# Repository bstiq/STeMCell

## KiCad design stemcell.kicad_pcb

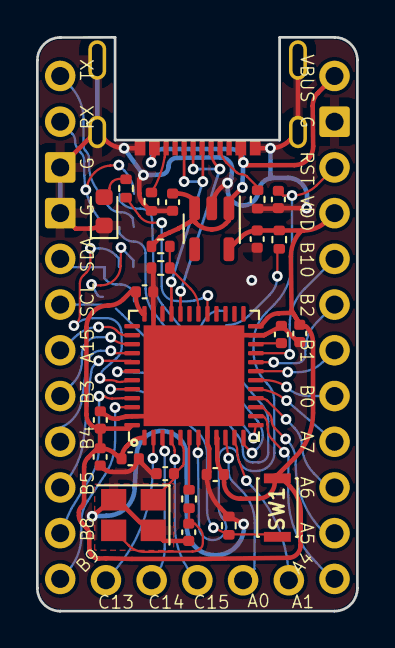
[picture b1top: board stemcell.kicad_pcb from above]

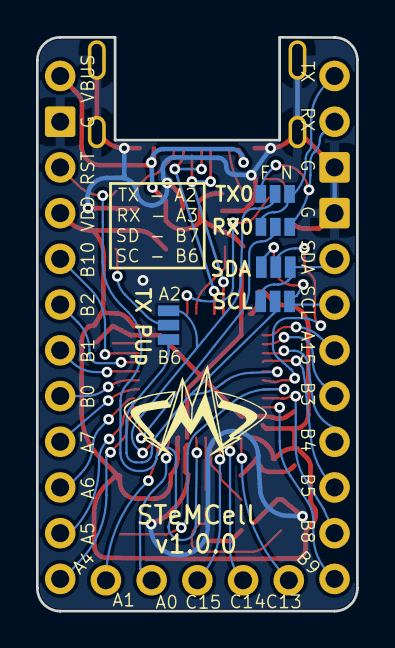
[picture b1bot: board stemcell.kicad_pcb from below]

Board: 2 copper layers, 17.8 x 31.9 mm, 34 parts (5 on the bottom side), 44 nets.

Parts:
C1: 10u; C_0402_1005Metric
C2, C3, C9: 4.7u; C_0402_1005Metric
C4, C5, C6, C7, C8, C12: 100n; C_0402_1005Metric
C10, C11: 20p; C_0402_1005Metric
D1: LED; LED_0603_1608Metric
J1: USB C Connector; USB-C-C168688
J2: Left; Pins12
J3: Right; Pins12
J4: Down; Pins5
JP1: TX0; SOLDER_JUMPER_3
JP2: RX0; SOLDER_JUMPER_3
JP3: SDA; SOLDER_JUMPER_3
JP4: SCL; SOLDER_JUMPER_3
JP5: TX PUp; SOLDER_JUMPER_3
R1: 220; R_0402_1005Metric
R2, R3: 5k1; R_0402_1005Metric
R4: 2k2; R_0402_1005Metric
R5: 4.7k; R_0402_1005Metric
R6, R7, R8: 10k; R_0402_1005Metric
SW1: Boot0; SW_SPST_CK_KXT3
U1: STM32F4x1CxUx; QFN-48-1EP_7x7mm_P0.5mm_EP5.6x5.6mm
U2: XC6220B331MR; SOT-23-5
Y1: HSE1 8Mhz 12pF; Crystal_SMD_3225-4Pin_3.2x2.5mm

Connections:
/BOOT0: R8.1, SW1.1 (A), U1.44 (BOOT0)
/CC1: J1.A5 (CC1), R2.1
/CC2: J1.B5 (CC2), R3.1
/HSE_IN: C10.1, U1.5 (PH0), Y1.1
/HSE_OUT: R1.2, U1.6 (PH1)
/HSE_OUT_1: C11.1, R1.1, Y1.3
/LED_R: D1.2 (A), R4.2
/NRST: C12.1, J3.3, U1.7 (NRST)
/PA0: J4.4, U1.10 (PA0)
/PA1: J4.5, U1.11 (PA1)
/PA2: JP1.2 (C), JP5.1 (A), U1.12 (PA2)
/PA3: JP2.2 (C), U1.13 (PA3)
/PA4: J3.12, U1.14 (PA4)
/PA5: J3.11, U1.15 (PA5)
/PA6: J3.10, U1.16 (PA6)
/PA7: J3.9, U1.17 (PA7)
/PA8: R4.1, U1.29 (PA8)
/PA9: R5.2, R6.1, U1.30 (PA9)
/PA15: J2.7, U1.38 (PA15)
/PB0: J3.8, U1.18 (PB0)
/PB1: J3.7, U1.19 (PB1)
/PB2: J3.6, U1.20 (PB2)
/PB3: J2.8, U1.39 (PB3)
/PB4: J2.9, U1.40 (PB4)
/PB5: J2.10, U1.41 (PB5)
/PB6: JP4.2 (C), JP5.3 (B), U1.42 (PB6)
/PB7: JP3.2 (C), U1.43 (PB7)
/PB8: J2.11, U1.45 (PB8)
/PB9: J2.12, U1.46 (PB9)
/PB10: J3.5, U1.21 (PB10)
/PC13: J4.1, U1.2 (PC13)
/PC14: J4.2, U1.3 (PC14)
/PC15: J4.3, U1.4 (PC15)
/RX0: J2.2, JP1.1 (A), JP2.1 (A)
/SCL: J2.6, JP3.1 (A), JP4.1 (A)
/SDA: J2.5, JP3.3 (B), JP4.3 (B)
/TX0: J2.1, JP1.3 (B), JP2.3 (B)
/TX_PULLUP: JP5.2 (C), R7.2
/USB_DN: J1.A7 (D-), J1.B7 (D-), U1.32 (PA11)
/USB_DP: J1.A6 (D+), J1.B6 (D+), U1.33 (PA12)
/VCAP1: C3.2, U1.22 (VCAP1)
GND: C1.2, C2.2, C3.1, C4.2, C5.2, C6.2, C7.2, C8.2, C9.2, C10.2, C11.2, C12.2, D1.1 (K), J1.A1 (GND), J1.S1 (SHIELD), J2.3, J2.4, J3.2, R2.2, R3.2, R6.2, R8.2, U1.8 (VSSA), U1.23 (VSS), U1.35 (VSS), U1.47 (VSS), U1.49 (VSS), U2.2 (GND), Y1.2, Y1.4
VBUS: C1.1, J1.A4 (VBUS), J3.1, R5.1, U2.1 (VIN), U2.3 (CE)
VDD: C2.1, C4.1, C5.1, C6.1, C7.1, C8.1, C9.1, J3.4, R7.1, SW1.2 (B), U1.1 (VBAT), U1.9 (VDDA), U1.24 (VDD), U1.36 (VDD), U1.48 (VDD), U2.5 (VOUT)

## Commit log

2022-02-14 remove gerbers
2022-02-14 labels
2022-02-14 silkscreen
2022-03-03 remove castellated pads
2022-03-03 change usb-c connector to part in stock at JLC
